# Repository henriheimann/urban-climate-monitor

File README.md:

# Urban Climate Monitor

Documentation: https://henriheimann.github.io/urban-climate-monitor/

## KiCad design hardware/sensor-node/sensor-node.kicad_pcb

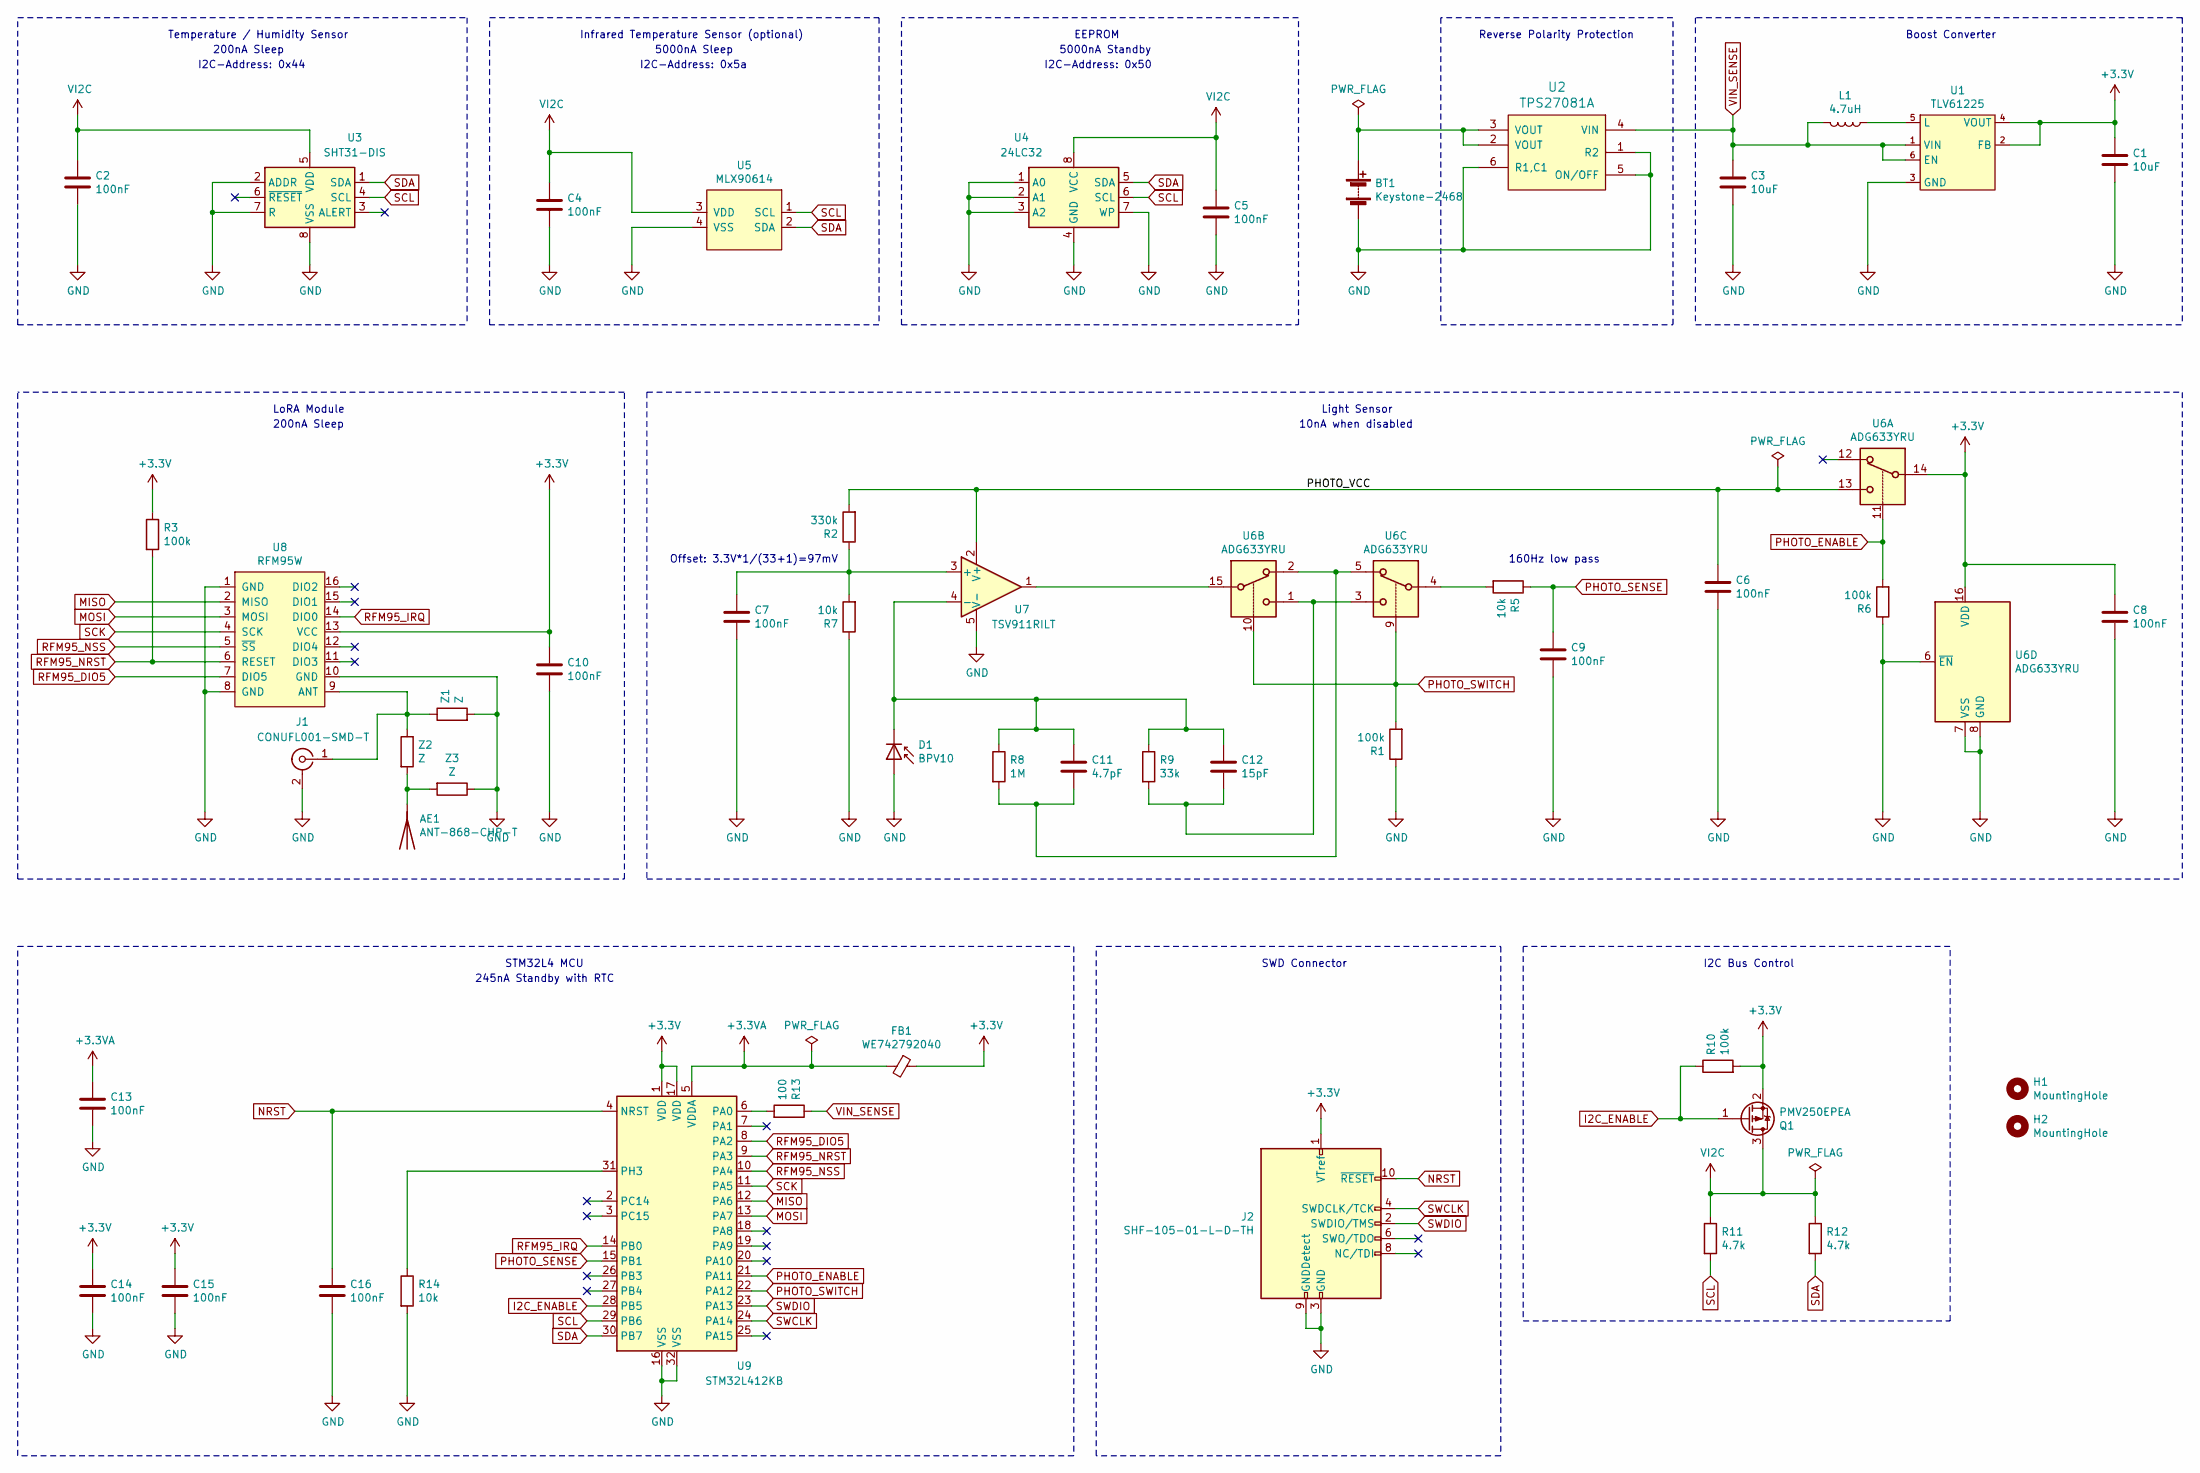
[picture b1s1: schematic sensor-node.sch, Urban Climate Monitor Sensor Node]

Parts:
AE1: ANT-868-CHP-T; Linx_ANT-868-CHP-T; mouser# 712-ANT-868-CHP-T; digikey# ANT-868-CHP-TCT-ND
BT1: Keystone-2468; BatteryHolder_Keystone_2468_2xAAA_NoSilkscreen; mouser# 534-2468; digikey# 36-2468-ND
C1, C3: 10uF; C_0805_2012Metric_Pad1.18x1.45mm_HandSolder; mouser# 80-C0805C106K9P7210; digikey# 399-C0805C106K9PAC7210CT-ND
C2, C4, C5, C6, C7, C8, C9, C10, C13, C14, C15, C16: 100nF; C_0805_2012Metric_Pad1.18x1.45mm_HandSolder; mouser# 80-C0805C103K8R; digikey# C0805C103K8RAC7800
C11: 4.7pF; C_0805_2012Metric_Pad1.18x1.45mm_HandSolder; mouser# 80-C0805C479C8HACTU; digikey# C0805C479C8HAC7800-ND
C12: 15pF; C_0805_2012Metric_Pad1.18x1.45mm_HandSolder; mouser# 80-C0805C150M8HACTU; digikey# C0805C150M8HAC7800
D1: BPV10; LED_D5.0mm_Clear; mouser# 782-BPV10; digikey# 751-1001-ND
FB1: WE742792040; L_0805_2012Metric_Pad1.15x1.40mm_HandSolder; mouser# 710-742792040; digikey# 732-1620-1-ND
H1, H2: MountingHole; MountingHole_2.2mm_M2
J1: CONUFL001-SMD-T; CONUFL001-SMD; mouser# 712-CONUFL001-SMD-T; digikey# CONUFL001-SMD-TCT-ND
J2: SHF-105-01-L-D-TH; mouser# 200-SHF10501LDTH; digikey# SAM11769-ND
L1: 4.7uH; L_Bourns-SRN4018_With3DModel; mouser# 652-SRN4018TA-4R7M; digikey# SRN4018TA-4R7MTR-ND
Q1: PMV250EPEA; SOT-23; mouser# 771-PMV250EPEAR; digikey# 1727-2303-1-ND
R1, R6: 100k; R_0805_2012Metric_Pad1.20x1.40mm_HandSolder; mouser# 603-RC0805FR-0710KL; digikey# 311-10.0KCRCT-ND
R2: 330k; R_0805_2012Metric_Pad1.20x1.40mm_HandSolder; mouser# 603-RC0805FR-07330KL; digikey# 311-330KCRCT-ND
R3, R10: 100k; R_0805_2012Metric_Pad1.20x1.40mm_HandSolder; mouser# 603-RC0805FR-07100KL; digikey# 311-100KCRCT-ND
R5, R7, R14: 10k; R_0805_2012Metric_Pad1.20x1.40mm_HandSolder; mouser# 603-RC0805FR-0710KL; digikey# 311-10.0KCRCT-ND
R8: 1M; R_0805_2012Metric_Pad1.20x1.40mm_HandSolder; mouser# 603-RC0805FR-071ML; digikey# 311-1.00MCRCT-ND
R9: 33k; R_0805_2012Metric_Pad1.20x1.40mm_HandSolder; mouser# 603-RC0805FR-0733KL; digikey# 311-33.0KCRCT-ND
R11, R12: 4.7k; R_0805_2012Metric_Pad1.20x1.40mm_HandSolder; mouser# 603-RC0805FR-074K7L; digikey# 311-4.70KCRCT-ND
R13: 100; R_0805_2012Metric_Pad1.15x1.40mm_HandSolder; mouser# 603-RC0805FR-07100RL; digikey# 311-100CRCT-ND
U1: TLV61225; SC-70-6; mouser# 595-TLV61225DCKR; digikey# 296-36756-1-ND
U2: TPS27081A; TSOT-23-6; mouser# 595-TPS27081ADDCR; digikey# 296-34970-1-ND
U3: SHT31-DIS; Sensirion_DFN-8-1EP_2.5x2.5mm_P0.5mm_EP1.1x1.7mm; mouser# 403-SHT31-DIS-F; digikey# 1649-1066-1-ND
U4: 24LC32; SOIC-8_3.9x4.9mm_P1.27mm; mouser# 579-24LC32AT-I/SN; digikey# 24LC32AT-I/SNCT-ND
U5: MLX90614; TO-39-4; mouser# 482-90614ESFBCC000TU; digikey# MLX90614ESF-BCC-000-TU-ND
U6: ADG633YRU; TSSOP-16_4.4x5mm_P0.65mm; mouser# 584-ADG633YRUZ; digikey# ADG633YRUZ-ND
U7: TSV911RILT; SOT-23-5; mouser# 511-TSV911RILT; digikey# 497-10538-1-ND
U8: RFM95W; mouser# 223-RFM95W-868S2; digikey# RFM95W-868S2-ND
U9: STM32L412KB; LQFP-32_7x7mm_P0.8mm; mouser# 511-STM32L412KBT6; digikey# 497-18229-ND
Z1, Z2, Z3: Z; R_0805_2012Metric_Pad1.20x1.40mm_HandSolder

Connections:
+3.3VA: C13.1, FB1.2, U9.5 (VDDA)
+3V3: C1.1, C8.1, C10.1, C14.1, C15.1, FB1.1, J2.1 (VTref), Q1.2 (S), R3.1, R10.2, U1.2 (FB), U1.4 (VOUT), U6.14, U6.16 (VDD), U8.13 (VCC), U9.1 (VDD), U9.17 (VDD)
/PHOTO_VCC: C6.1, R2.2, U6.13, U7.2 (V+)
GND: BT1.2 (-), C1.2, C2.2, C3.2, C4.2, C5.2, C6.2, C7.2, C8.2, C9.2, C10.2, C13.2, C14.2, C15.2, C16.2, D1.2 (A), J1.2 (Ext), J2.3 (GND), J2.5 (GND), J2.9 (GNDDetect), R1.1, R6.1, R7.1, R14.2, U1.3 (GND), U2.1 (R2), U2.5 (ON/OFF), U2.6 (R1,C1), U3.2 (ADDR), U3.7 (R), U3.8 (VSS), U3.9 (VSS), U4.1 (A0), U4.2 (A1), U4.3 (A2), U4.4 (GND), U4.7 (WP), U5.4 (VSS), U6.6 (~EN), U6.7 (VSS), U6.8 (GND), U7.5 (V-), U8.1 (GND), U8.8 (GND), U8.10 (GND), U9.16 (VSS), U9.32 (VSS), Z1.2, Z3.1
I2C_ENABLE: Q1.1 (G), R10.1, U9.28 (PB5)
MISO: U8.2 (MISO), U9.12 (PA6)
MOSI: U8.3 (MOSI), U9.13 (PA7)
NRST: C16.1, J2.10 (~RESET~), U9.4 (NRST)
unnamed: AE1.1, Z2.2, Z3.2
unnamed: BT1.1 (+), U2.2 (VOUT), U2.3 (VOUT)
unnamed: C7.1, R2.1, R7.2, U7.3 (+)
unnamed: C11.1, C12.1, D1.1 (K), R8.1, R9.1, U7.4 (-)
unnamed: C11.2, R8.2, U6.2, U6.5
unnamed: C12.2, R9.2, U6.1, U6.3
unnamed: J1.1 (In), U8.9 (ANT), Z1.1, Z2.1
unnamed: L1.1, U1.5 (L)
unnamed: R5.2, U6.4
unnamed: R13.2, U9.6 (PA0)
unnamed: R14.1, U9.31 (PH3)
unnamed: U6.15, U7.1
PHOTO_ENABLE: R6.2, U6.11, U9.21 (PA11)
PHOTO_SENSE: C9.1, R5.1, U9.15 (PB1)
PHOTO_SWITCH: R1.2, U6.9, U6.10, U9.22 (PA12)
RFM95_DIO5: U8.7 (DIO5), U9.8 (PA2)
RFM95_IRQ: U8.14 (DIO0), U9.14 (PB0)
RFM95_NRST: R3.2, U8.6 (RESET), U9.9 (PA3)
RFM95_NSS: U8.5 (~SS), U9.10 (PA4)
SCK: U8.4 (SCK), U9.11 (PA5)
SCL: R11.2, U3.4 (SCL), U4.6 (SCL), U5.1 (SCL), U9.29 (PB6)
SDA: R12.2, U3.1 (SDA), U4.5 (SDA), U5.2 (SDA), U9.30 (PB7)
SWCLK: J2.4 (SWDCLK/TCK), U9.24 (PA14)
SWDIO: J2.2 (SWDIO/TMS), U9.23 (PA13)
VI2C: C2.1, C4.1, C5.1, Q1.3 (D), R11.1, R12.1, U3.5 (VDD), U4.8 (VCC), U5.3 (VDD)
VIN_SENSE: C3.1, L1.2, R13.1, U1.1 (VIN), U1.6 (EN), U2.4 (VIN)

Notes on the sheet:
Reverse Polarity Protection
Boost Converter
SWD Connector
STM32L4 MCU
I2C-Address: 0x44
I2C-Address: 0x5a
Offset: 3.3V*1/(33+1)=97mV
Infrared Temperature Sensor (optional)
Temperature / Humidity Sensor
LoRA Module
Light Sensor
I2C-Address: 0x50
EEPROM
5000nA Sleep
200nA Sleep
5000nA Standby
245nA Standby with RTC
10nA when disabled
160Hz low pass
I2C Bus Control

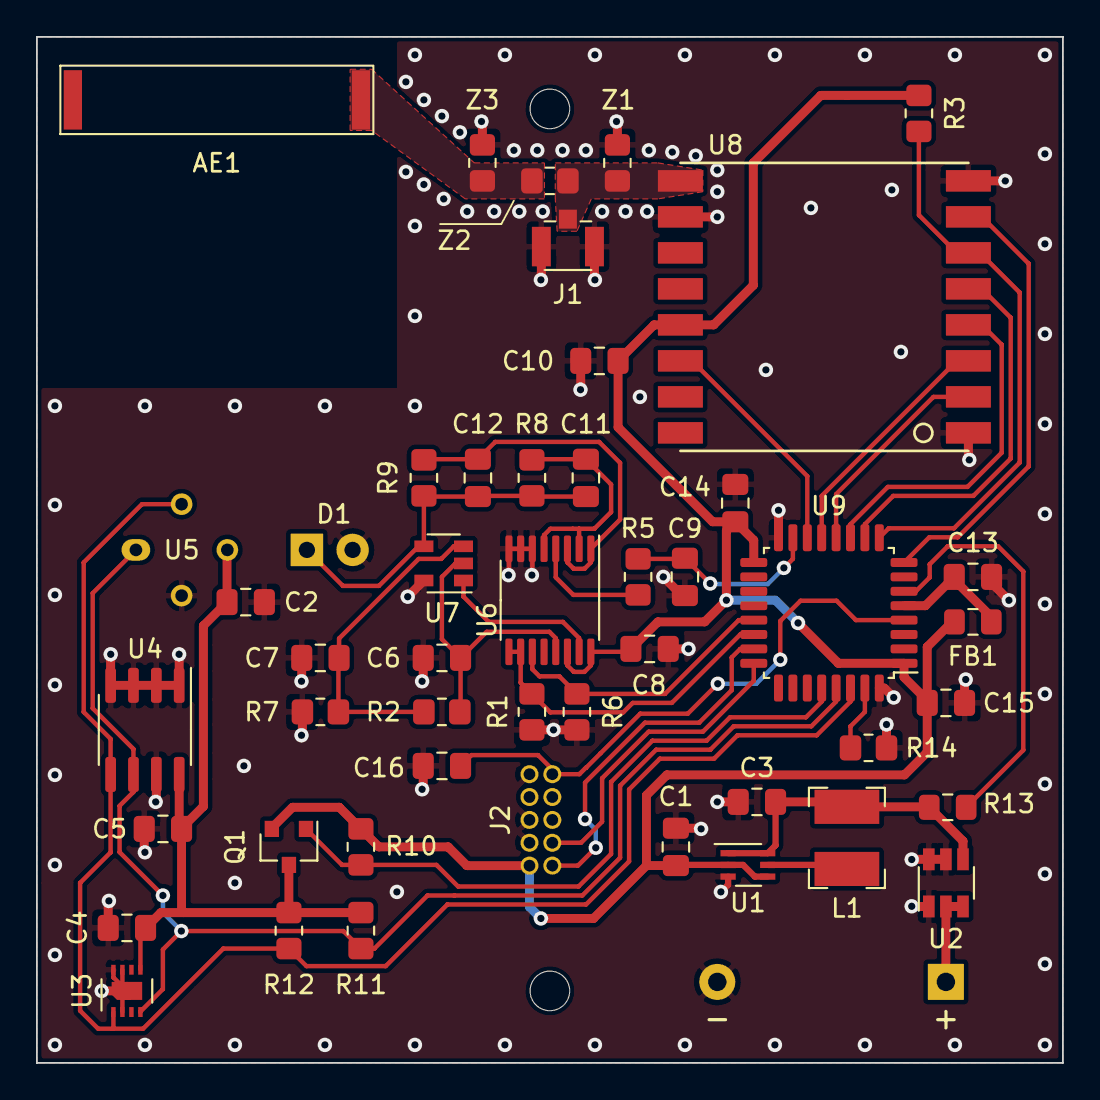
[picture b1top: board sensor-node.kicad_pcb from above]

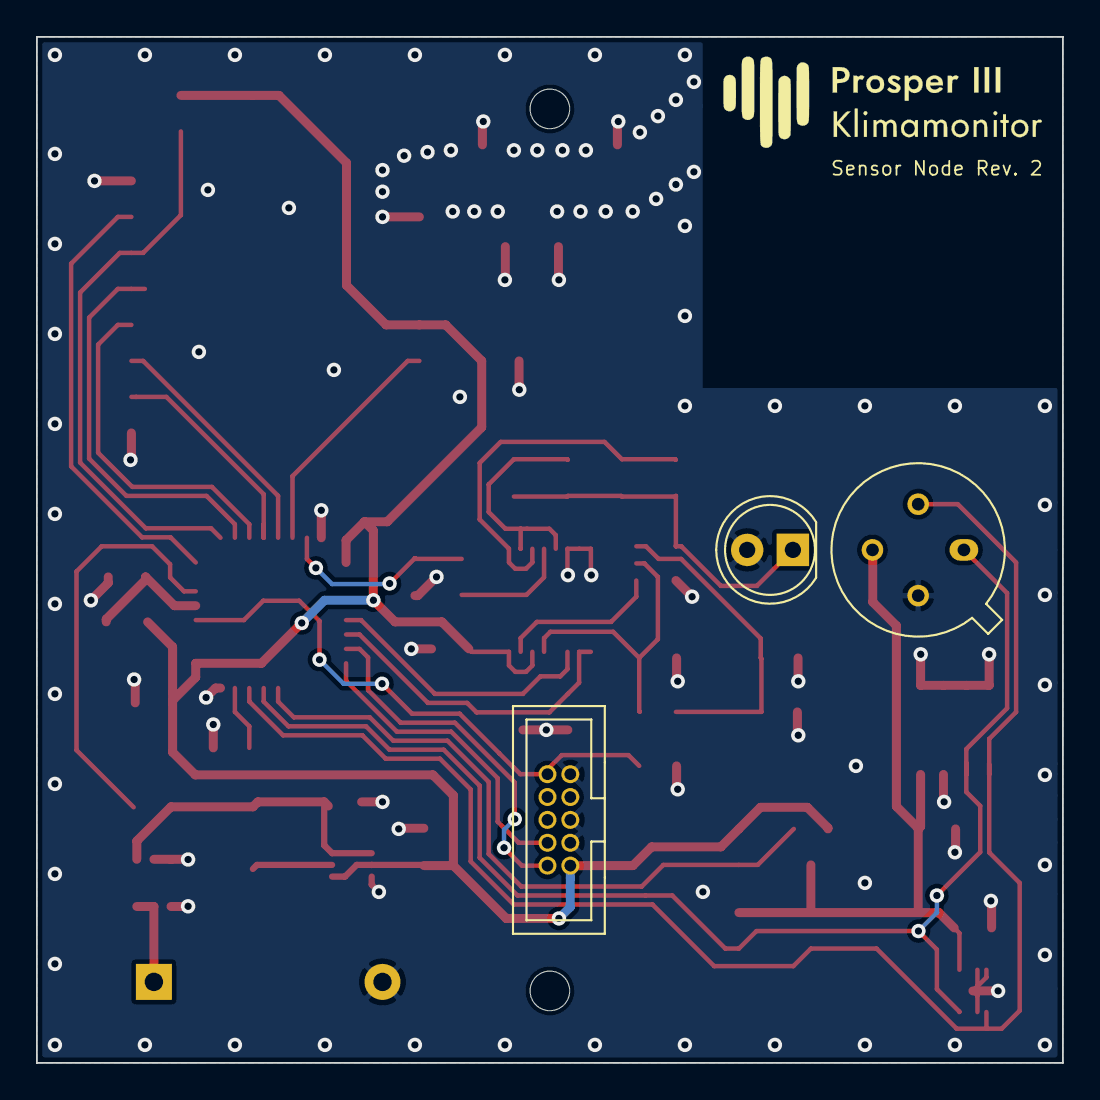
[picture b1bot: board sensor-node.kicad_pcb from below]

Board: 2 copper layers, 57.0 x 57.0 mm, 51 parts (4 on the bottom side), 34 nets.

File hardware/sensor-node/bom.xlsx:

| Number of Boards: | 3
Source | Reference | Value | Quantity Abs | Quantity | Manufacturer # | Digikey # | Digikey STK | Mouser # | Mouser STK | Price
BOM | AE1 |  |  | 1 | ANT-868-CHP-T | ANT-868-CHP-TCT-ND | 2.3199999999999998 |  |  | 6.9599999999999991
BOM | BT1 |  |  | 1 | 2468 |  |  | 534-2468 | 1.1499999999999999 | 3.4499999999999997
BOM | C11 | 4.7pF |  | 1 | C0805C479C8HACTU |  |  | 80-C0805C479C8HACTU | 8.5000000000000006E-2 | 0.255
BOM | C12 | 15pF |  | 1 | C0805C150M8HACTU |  |  | 80-C0805C150M8HACTU | 8.5000000000000006E-2 | 0.255
BOM | C2 C4 C5 C6 C7 C8 C9 C10 C13 C14 C15 C16 | 100nF |  | 12 | C0805C103K8RACTU |  |  | 80-C0805C103K8R | 0.152 | 5.4719999999999995
BOM | C1 C3 | 10uF |  | 2 | C0805C106K9PAC7210 |  |  | 80-C0805C106K9P7210 | 0.11899999999999999 | 0.71399999999999997
BOM | D1 |  |  | 1 | BPV10 |  |  | 782-BPV10 | 0.93200000000000005 | 2.7960000000000003
BOM | FB1 |  |  | 1 | 742792040 |  |  | 710-742792040 | 0.186 | 0.55800000000000005
BOM | J1 |  |  | 1 | CONUFL001-SMD-T |  |  | 712-CONUFL001-SMD-T | 0.52500000000000002 | 1.5750000000000002
BOM | J2 |  |  | 1 | SHF-105-01-L-D-TH |  |  | 200-SHF10501LDTH | 2.29 | 6.87
BOM | L1 | 4.7uH |  | 1 | SRN4018TA-4R7M | SRN4018TA-4R7MCT-ND | 0.41 |  |  | 1.23
BOM | Q1 |  |  | 1 | PMV250EPEA |  |  | 771-PMV250EPEAR | 0.34 | 1.02
BOM | R11 R12 | 4.7k |  | 2 | RC0805FR-074K7L |  |  | 603-RC0805FR-074K7L | 0.11 | 0.66
BOM | R13 | 100 |  | 1 | RC0805FR-07100RL |  |  | 603-RC0805FR-07100RL | 0.11 | 0.33
BOM | R5 R6 R7 R14 | 10k |  | 4 | RC0805FR-0710KL |  |  | 603-RC0805FR-0710KL | 0.11 | 1.32
BOM | R2 | 330k |  | 1 | RC0805FR-07330KL |  |  | 603-RC0805FR-07330KL | 0.11 | 0.33
BOM | R3 R4 R10 | 100k |  | 3 | RC0805FR-07100KL |  |  | 603-RC0805FR-07100KL | 0.11 | 0.99
BOM | R8 | 1M |  | 1 | RC0805FR-071ML |  |  | 603-RC0805FR-071ML | 8.5000000000000006E-2 | 0.255
BOM | R9 | 33k |  | 1 | RC0805FR-0733KL |  |  | 603-RC0805FR-0733KL | 0.11 | 0.33
BOM | U1 |  |  | 1 | TLV61225DCKR |  |  | 595-TLV61225DCKR | 0.86 | 2.58
BOM | U2 |  |  | 1 | TPS27081ADDCR |  |  | 595-TPS27081ADDCR | 0.66 | 1.98
BOM | U3 |  |  | 1 | SHT31-DIS-F2.5kS |  |  | 403-SHT31-DIS-F | 5.4 | 16.200000000000003
BOM | U4 |  |  | 1 | 24LC32AT-I/SN |  |  | 579-24LC32AT-I/SN | 0.28799999999999998 | 0.86399999999999988
BOM | U5 |  |  | 1 | MLX90614ESF-BCC-000-TU | MLX90614ESF-BCC-000-TU-ND | 20.78 |  |  | 62.34
BOM | U6 |  |  | 1 | ADG633YRUZ |  |  | 584-ADG633YRUZ | 2.2400000000000002 | 6.7200000000000006
BOM | U7 |  |  | 1 | TSV911RILT |  |  | 511-TSV911RILT | 0.63 | 1.8900000000000001
BOM | U8 |  |  | 1 | RFM95W-868 | RFM95W-868S2-ND | 12.2 |  |  | 36.599999999999994
BOM | U9 |  |  | 1 | STM32L412KBT6 |  |  | 511-STM32L412KBT6 | 3.06 | 9.18
EQUIP |  |  | 1 |  | CSH-SGFB-100-UFFR |  |  | 712-CSH-SGFB100-UFFR | 4.87 | 4.87
EQUIP |  |  | 1 |  | ADP-SMAM-SMAM-G |  |  | 712-ADP-SMAM-SMAM-G | 5.52 | 5.52
 |  |  |  |  |  |  |  |  |  | 184.114

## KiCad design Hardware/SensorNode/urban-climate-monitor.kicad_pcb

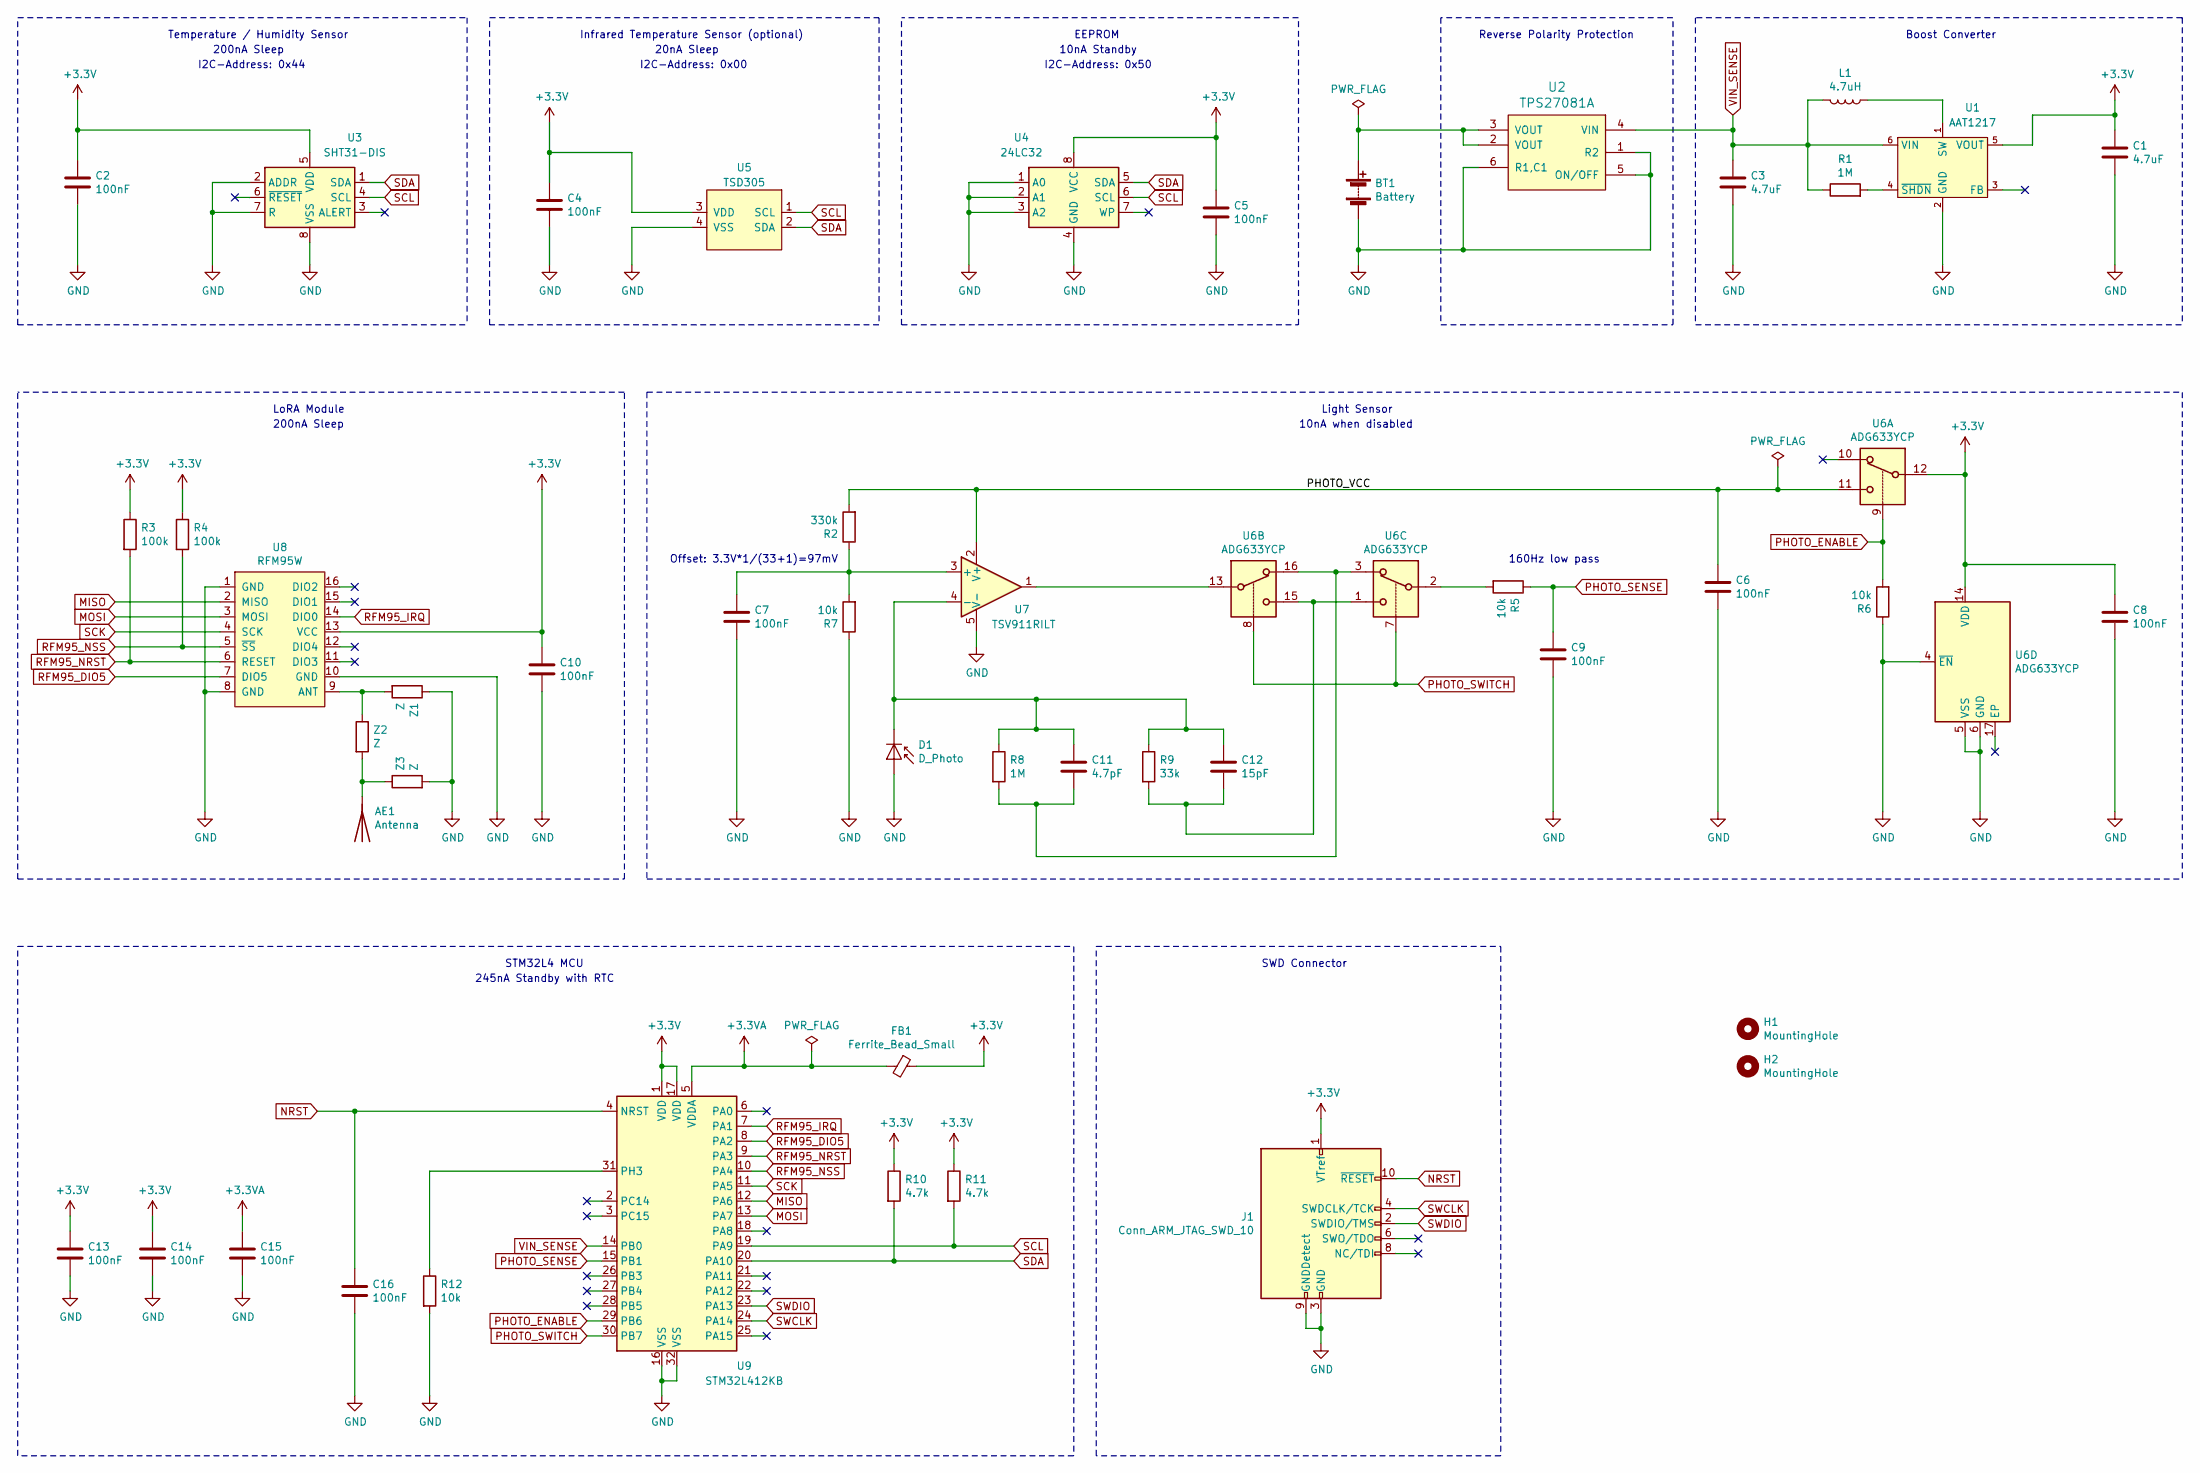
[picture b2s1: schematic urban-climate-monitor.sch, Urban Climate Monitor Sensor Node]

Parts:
AE1: Antenna; 868MHZ_TI_DNO24
BT1: Battery; BatteryHolder_Keystone_2468_2xAAA_NoSilkscreen
C1, C3: 4.7uF; C_0805_2012Metric_Pad1.18x1.45mm_HandSolder
C2, C4, C5, C6, C7, C8, C9, C10, C13, C14, C15, C16: 100nF; C_0805_2012Metric_Pad1.18x1.45mm_HandSolder
C11: 4.7pF; C_0805_2012Metric_Pad1.18x1.45mm_HandSolder
C12: 15pF; C_0805_2012Metric_Pad1.18x1.45mm_HandSolder
D1: D_Photo; LED_D5.0mm_Clear
FB1: Ferrite_Bead_Small; L_0805_2012Metric_Pad1.05x1.20mm_HandSolder
H1, H2: MountingHole; MountingHole_2.2mm_M2
J1: Conn_ARM_JTAG_SWD_10; Amphenol_FCI_ShroudedSocket_2x05_P1.27mm_Vertical_SMD
L1: 4.7uH; L_Bourns-SRN4018_With3DModel
R1, R8: 1M; R_0805_2012Metric_Pad1.20x1.40mm_HandSolder
R2: 330k; R_0805_2012Metric_Pad1.20x1.40mm_HandSolder
R3, R4: 100k; R_0805_2012Metric_Pad1.20x1.40mm_HandSolder
R5, R6, R7, R12: 10k; R_0805_2012Metric_Pad1.20x1.40mm_HandSolder
R9: 33k; R_0805_2012Metric_Pad1.20x1.40mm_HandSolder
R10, R11: 4.7k; R_0805_2012Metric_Pad1.20x1.40mm_HandSolder
U1: AAT1217; TSOT-23-6_HandSoldering
U2: TPS27081A; TSOT-23-6_HandSoldering
U3: SHT31-DIS; Sensirion_DFN-8-1EP_2.5x2.5mm_P0.5mm_EP1.1x1.7mm
U4: 24LC32; SOIC-8_3.9x4.9mm_P1.27mm
U5: TSD305
U6: ADG633YCP; TSSOP-16_4.4x5mm_P0.65mm
U7: TSV911RILT; SOT-23-5
U8: RFM95W
U9: STM32L412KB; LQFP-32_7x7mm_P0.8mm
Z1, Z2, Z3: Z; R_0805_2012Metric_Pad1.20x1.40mm_HandSolder

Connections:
+3.3VA: C15.1, FB1.2, U9.5 (VDDA)
+3V3: C1.1, C2.1, C4.1, C5.1, C8.1, C10.1, C13.1, C14.1, FB1.1, J1.1 (VTref), R3.1, R4.1, R10.1, R11.1, U1.5 (VOUT), U3.5 (VDD), U4.8 (VCC), U5.3 (VDD), U6.12, U6.14 (VDD), U8.13 (VCC), U9.1 (VDD), U9.17 (VDD)
/PHOTO_VCC: C6.1, R2.2, U6.11, U7.2 (V+)
GND: BT1.2 (-), C1.2, C2.2, C3.2, C4.2, C5.2, C6.2, C7.2, C8.2, C9.2, C10.2, C13.2, C14.2, C15.2, C16.2, D1.2 (A), J1.3 (GND), J1.5 (GND), J1.9 (GNDDetect), R6.1, R7.1, R12.2, U1.2 (GND), U2.1 (R2), U2.5 (ON/OFF), U2.6 (R1,C1), U3.2 (ADDR), U3.7 (R), U3.8 (VSS), U3.9 (VSS), U4.1 (A0), U4.2 (A1), U4.3 (A2), U4.4 (GND), U5.4 (VSS), U6.4 (~EN), U6.5 (VSS), U6.6 (GND), U7.5 (V-), U8.1 (GND), U8.8 (GND), U8.10 (GND), U9.16 (VSS), U9.32 (VSS), Z1.1, Z3.2
MISO: U8.2 (MISO), U9.12 (PA6)
MOSI: U8.3 (MOSI), U9.13 (PA7)
NRST: C16.1, J1.10 (~RESET~), U9.4 (NRST)
unnamed: AE1.1, Z2.2, Z3.1
unnamed: BT1.1 (+), U2.2 (VOUT), U2.3 (VOUT)
unnamed: C7.1, R2.1, R7.2, U7.3 (+)
unnamed: C11.1, C12.1, D1.1 (K), R8.1, R9.1, U7.4 (-)
unnamed: C11.2, R8.2, U6.3, U6.16
unnamed: C12.2, R9.2, U6.1, U6.15
unnamed: L1.1, U1.1 (SW)
unnamed: R1.2, U1.4 (~SHDN)
unnamed: R5.2, U6.2
unnamed: R12.1, U9.31 (PH3)
unnamed: U6.13, U7.1
unnamed: U8.9 (ANT), Z1.2, Z2.1
PHOTO_ENABLE: R6.2, U6.9, U9.29 (PB6)
PHOTO_SENSE: C9.1, R5.1, U9.15 (PB1)
PHOTO_SWITCH: U6.7, U6.8, U9.30 (PB7)
RFM95_DIO5: U8.7 (DIO5), U9.8 (PA2)
RFM95_IRQ: U8.14 (DIO0), U9.7 (PA1)
RFM95_NRST: R3.2, U8.6 (RESET), U9.9 (PA3)
RFM95_NSS: R4.2, U8.5 (~SS), U9.10 (PA4)
SCK: U8.4 (SCK), U9.11 (PA5)
SCL: R11.2, U3.4 (SCL), U4.6 (SCL), U5.1 (SCL), U9.19 (PA9)
SDA: R10.2, U3.1 (SDA), U4.5 (SDA), U5.2 (SDA), U9.20 (PA10)
SWCLK: J1.4 (SWDCLK/TCK), U9.24 (PA14)
SWDIO: J1.2 (SWDIO/TMS), U9.23 (PA13)
VIN_SENSE: C3.1, L1.2, R1.1, U1.6 (VIN), U2.4 (VIN), U9.14 (PB0)

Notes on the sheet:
Reverse Polarity Protection
Boost Converter
SWD Connector
STM32L4 MCU
I2C-Address: 0x44
I2C-Address: 0x00
Offset: 3.3V*1/(33+1)=97mV
Infrared Temperature Sensor (optional)
Temperature / Humidity Sensor
LoRA Module
Light Sensor
I2C-Address: 0x50
EEPROM
20nA Sleep
200nA Sleep
10nA Standby
245nA Standby with RTC
10nA when disabled
160Hz low pass

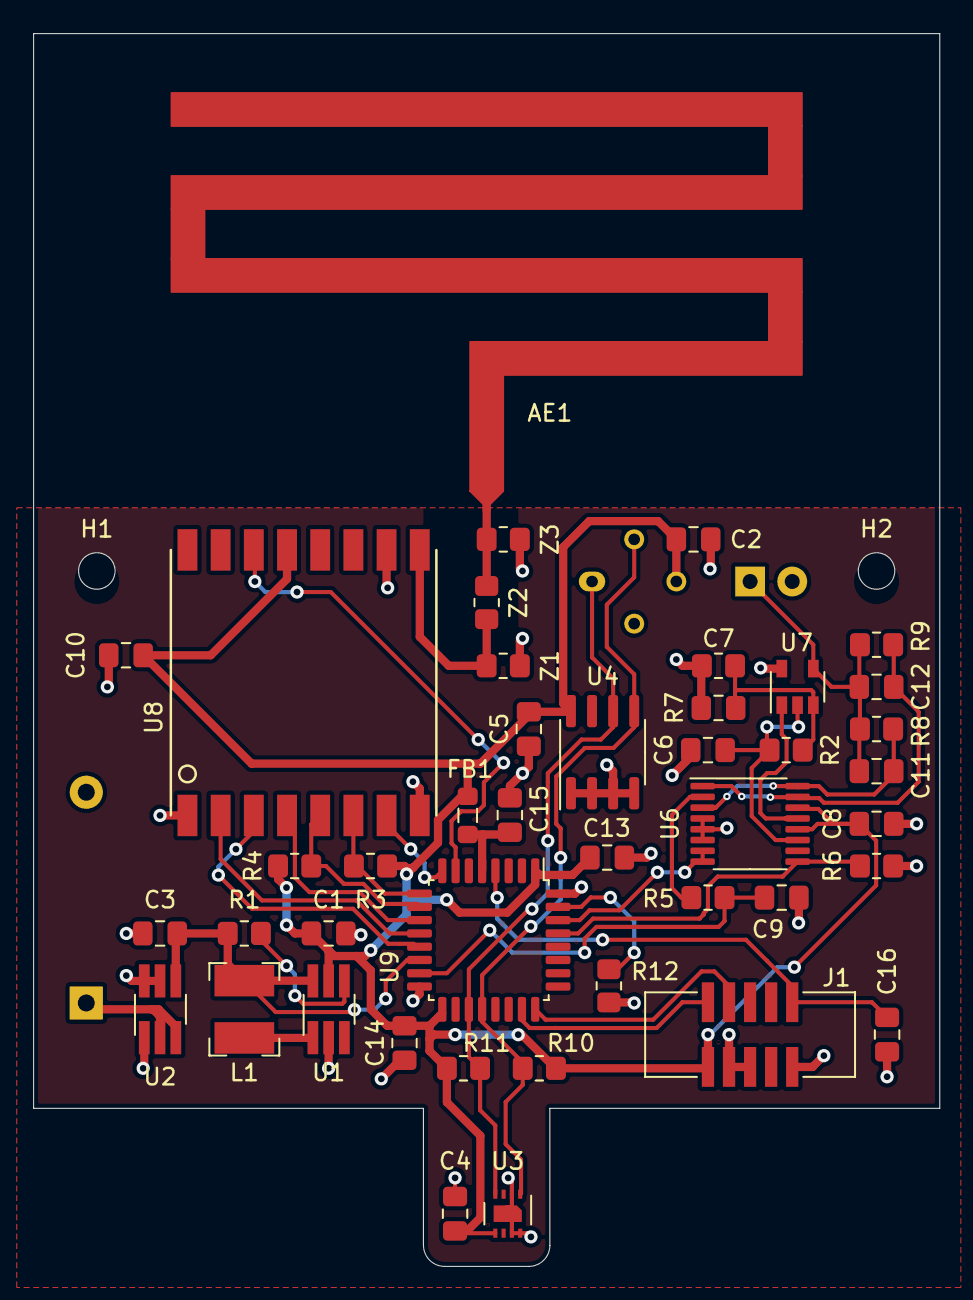
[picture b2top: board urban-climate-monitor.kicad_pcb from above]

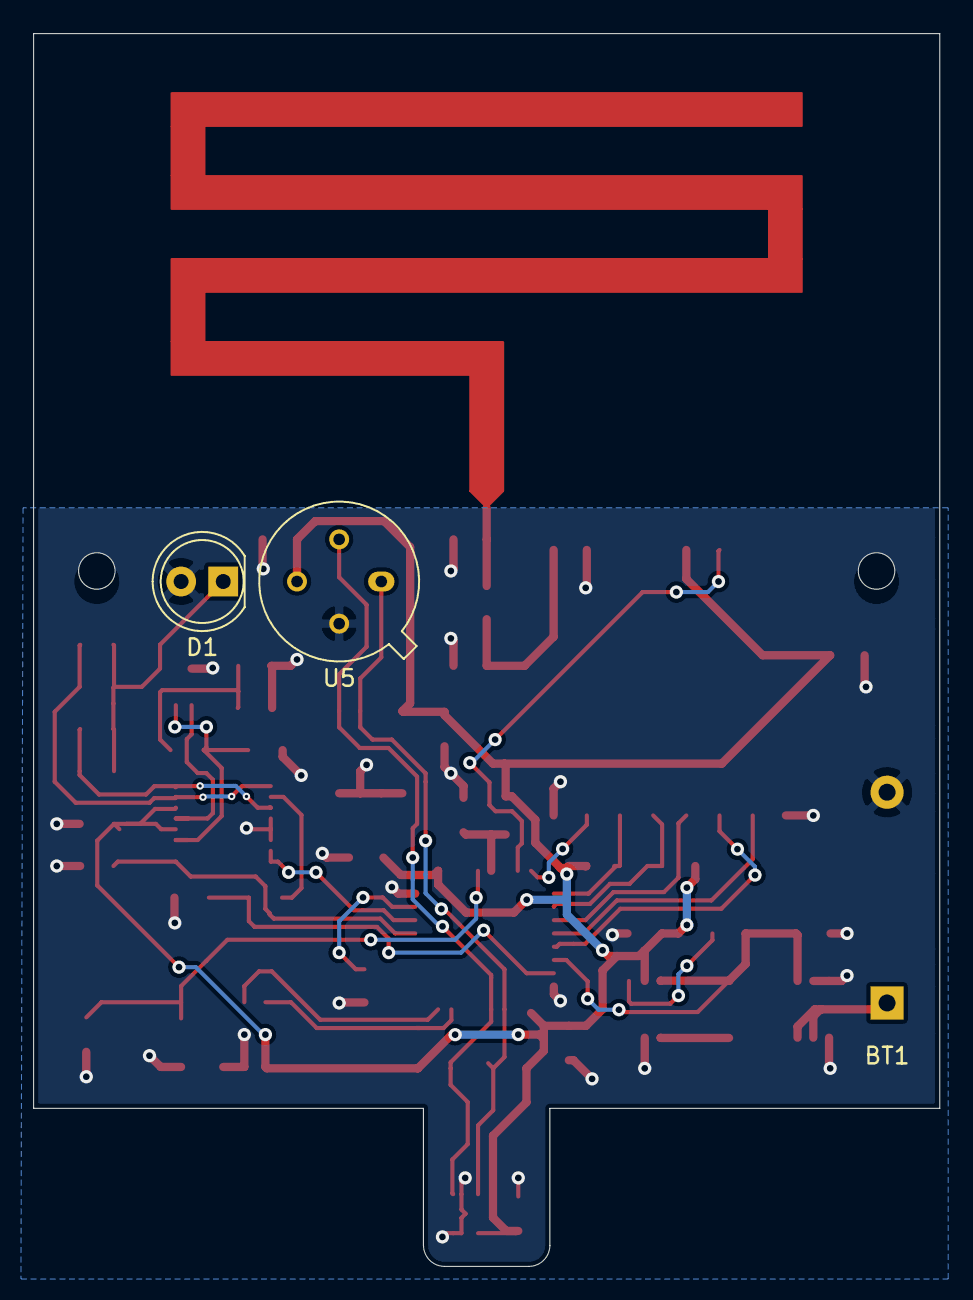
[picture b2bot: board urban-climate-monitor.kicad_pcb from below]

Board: 2 copper layers, 54.6 x 74.3 mm, 48 parts (3 on the bottom side), 32 nets.

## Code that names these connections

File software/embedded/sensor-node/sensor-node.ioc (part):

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PA0-CK_IN.GPIO_Label=VIN_SENSE
PA0-CK_IN.GPIOParameters=GPIO_Label
PA2.GPIO_PuPd=GPIO_PULLUP
PA6.Mode=Full_Duplex_Master
PA14\ (JTCK/SWCLK).GPIOParameters=GPIO_Label
Mcu.UserName=STM32L412KBUx
PA12.GPIOParameters=GPIO_PuPd,GPIO_Label
PA11.GPIOParameters=GPIO_Label
PA3.GPIOParameters=GPIO_Label
PB0.GPIO_Label=RFM95_DIO0
PA2.GPIOParameters=GPIO_PuPd,GPIO_Label
PB5.GPIOParameters=PinState,GPIO_Label
PA14\ (JTCK/SWCLK).Signal=SYS_JTCK-SWCLK
PA12.Signal=GPIO_Output
PB6.Signal=I2C1_SCL
PB5.PinState=GPIO_PIN_SET
PB6.Mode=I2C
RCC.HSE_VALUE=8000000
PA0-CK_IN.Signal=ADCx_IN5
PB0.GPIOParameters=GPIO_PuPd,GPIO_Label
PA13\ (JTMS/SWDIO).GPIO_Label=SWDIO
PB1.GPIO_Label=PHOTO_SENSE
PB7.Signal=I2C1_SDA
PA14\ (JTCK/SWCLK).Mode=Serial_Wire
PB6.GPIO_PuPdOD=GPIO_NOPULL
PB6.GPIOParameters=GPIO_PuPdOD
Mcu.Package=UFQFPN32
PA6.Signal=SPI1_MISO
PB1.Signal=ADCx_IN16
PA2.GPIO_Label=RFM95_DIO5
PA14\ (JTCK/SWCLK).GPIO_Label=SWCLK
PB5.GPIO_Label=I2C_ENABLE
PA12.GPIO_PuPd=GPIO_PULLDOWN
PA4.GPIO_Label=RFM95_NSS
PA3.Signal=GPIO_Output
PA5.Mode=Full_Duplex_Master
PA7.Mode=Full_Duplex_Master
PA13\ (JTMS/SWDIO).Mode=Serial_Wire
PA11.GPIO_Label=PHOTO_ENABLE
boardIOC=true
PA13\ (JTMS/SWDIO).GPIOParameters=GPIO_Label
PA12.GPIO_Label=PHOTO_SWITCH
PA4.PinState=GPIO_PIN_SET
PB7.GPIOParameters=GPIO_PuPdOD
PA5.Signal=SPI1_SCK
board=NUCLEO-L412KB
PA4.GPIOParameters=PinState,GPIO_Label
PB7.GPIO_PuPdOD=GPIO_NOPULL
Mcu.Name=STM32L412KBUx
PA2.Signal=GPIO_Input
PA4.Signal=GPIO_Output
RCC.SYSCLKFreq_VALUE=32000000
PB5.Signal=GPIO_Output
PB7.Mode=I2C
PA11.Signal=GPIO_Output
PB0.Signal=GPIO_Input
PB0.GPIO_PuPd=GPIO_PULLUP
PA13\ (JTMS/SWDIO).Signal=SYS_JTMS-SWDIO
PA3.GPIO_Label=RFM95_NRST
PB1.GPIOParameters=GPIO_Label
PA7.Signal=SPI1_MOSI

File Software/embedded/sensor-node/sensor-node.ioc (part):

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PA6.Mode=Full_Duplex_Master
PA14\ (JTCK/SWCLK).GPIOParameters=GPIO_Label
Mcu.UserName=STM32L412KBUx
PA3.GPIOParameters=PinState,GPIO_Label
PB0.GPIO_Label=VIN_SENSE
PB6.GPIO_Label=PHOTO_ENABLE
PA2.GPIOParameters=GPIO_Label
PA14\ (JTCK/SWCLK).Signal=SYS_JTCK-SWCLK
PB6.Signal=GPIO_Output
RCC.HSE_VALUE=8000000
PB0.GPIOParameters=GPIO_Label
PA13\ (JTMS/SWDIO).GPIO_Label=SWDIO
PA1.GPIOParameters=GPIO_Label
PB1.GPIO_Label=PHOTO_SENSE
PB7.Signal=GPIO_Output
PA14\ (JTCK/SWCLK).Mode=Serial_Wire
PB6.GPIOParameters=GPIO_Label
PB7.GPIO_Label=PHOTO_SWITCH
Mcu.Package=UFQFPN32
PA6.Signal=SPI1_MISO
PB1.Signal=ADCx_IN16
PA2.GPIO_Label=RFM95_DIO5
PA10.Signal=I2C1_SDA
PA14\ (JTCK/SWCLK).GPIO_Label=SWCLK
PA4.GPIO_Label=RFM95_NSS
PA3.Signal=GPIO_Output
PA5.Mode=Full_Duplex_Master
PA7.Mode=Full_Duplex_Master
PA13\ (JTMS/SWDIO).Mode=Serial_Wire
PA10.Mode=I2C
boardIOC=true
PA13\ (JTMS/SWDIO).GPIOParameters=GPIO_Label
PA9.Mode=I2C
PA4.PinState=GPIO_PIN_SET
PB7.GPIOParameters=GPIO_Label
PA9.Signal=I2C1_SCL
PA1.Signal=GPXTI1
PA5.Signal=SPI1_SCK
board=NUCLEO-L412KB
PA1.GPIO_Label=RFM95_IRQ
PA4.GPIOParameters=PinState,GPIO_Label
Mcu.Name=STM32L412KBUx
PA2.Signal=GPIO_Input
PA4.Signal=GPIO_Output
RCC.SYSCLKFreq_VALUE=32000000
PA3.PinState=GPIO_PIN_SET
PB0.Signal=ADCx_IN15
PA13\ (JTMS/SWDIO).Signal=SYS_JTMS-SWDIO
PA3.GPIO_Label=RFM95_NRST
PB1.GPIOParameters=GPIO_Label
PA7.Signal=SPI1_MOSI

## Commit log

2020-10-19 Add initial embedded software version and update schematic
2020-10-23 Update prototype pin assignment
2020-10-23 Add required submodules to prototype project
2020-10-23 Hello world from MCU
2020-10-26 Remove rfm9x submodule, sht3x test in main application
2020-10-26 Add new rfm95 submodule
2020-10-26 Move embedded projects to subdirectory
2020-10-26 Update submodules for new subdirectory
2020-10-26 Ignore build directory, update cmake workflow
2020-10-26 Checkout submodules in cmake_urbanclimatemonitorprototype.yml
2020-10-26 Rename prototype project to PrototypeNode
2020-10-26 Initial work on rfm95 integration
2020-10-29 Updates RFM95 integration and first test
2020-10-30 Update rfm95 library version
2020-10-30 Add lora frame couting via eeprom
2020-10-30 Include EEPROM in schematic
2020-10-30 Add photo sensing implementation
2020-11-02 Create first revision of PCB, add CubeMX project for PCB sensor node
2020-11-02 Update directory structure
2020-11-03 Test KiCad action docs generation
2020-11-03 Trigger pipeline
2020-11-03 Fix warnings of electrical rules check
2020-11-11 Add photo enable pin, add deployment compose
2020-11-11 Upload only pdfs as artifact
2020-11-11 Fix pipeline docs path
2020-11-12 Add TIG stack to deployment
2020-11-12 Move grafana behind nginx reverse proxy
2020-11-12 Add deployment readme
2020-11-12 Add angular frontend
2020-11-12 Add frontend to deployment
2020-11-12 Create deploy script
2020-11-12 Add SSL to deployed site
2020-11-12 Add ssl renew cron
2020-11-15 Change folder layout, add new version pcb layout
2020-11-15 Fix folder capitalisation
2020-11-15 Try fix folder capitalisation again part 1
2020-11-15 Try fix folder capitalisation again part 2
2020-11-15 Try fix submodules part 1
2020-11-15 Try fix submodules part 2
2020-11-16 Add standby mode between measurements and photocurrent measurement
2020-11-19 Update schema to include I2C voltage switching
2020-11-19 Update PCB, add debugging printouts to application
2020-11-19 Test export of board plot
2020-11-19 Fix workflow schematic and board references
2020-11-19 Only upload required files
2020-11-20 Fix timeouts for systick overflow handling
2020-11-21 Update PCB for enclosure
2020-11-22 Add 3d model to infrared temperature sensor
2020-11-22 Add design resources and logo to PCB silkscreen
2020-11-28 Add picket fence vias
2020-11-29 Switch to available boost converter
2020-11-29 Update PCB for new boost converter
2020-11-29 Fix ERC & DRC errors
2020-11-29 Fix ADG633YRU pinout
2020-11-29 Update C9 pad 2
2020-11-29 Perform parts pinout check
2020-11-29 Add BOM excel sheet
2020-12-28 Setup sensor-node embedded project
2020-12-28 Move eeprom to submodule
2020-12-28 Update submodules remotes
2020-12-28 Add sensor-node build workflow
2020-12-31 First implementation of MLX90614 driver
2021-01-09 Work on sensor-node application
2021-01-09 Move RFM95 initialisation
2021-01-11 Fix rounding and wait for MLX90614
2021-01-11 Fix PCB problems for Rev. 2
2021-01-11 Move Via
2021-01-25 Add nanovna calibration
2021-02-26 Fix InfluxDB version to 1.8, add local test deployment possibility
2021-02-27 Add three.js canvas
2021-03-08 Add basic backend setup
2021-03-13 Update design, work on backend
2021-03-22 Work on user and sensor controllers and services
2021-03-23 Add SensorService unit tests
2021-03-23 Remove prototype embedded software
2021-03-23 Remove submodules
2021-03-23 Readd submodules
2021-03-23 Remove MLX90614 code to be replaced by submodule
2021-03-23 Add MLX90614 submodule
2021-03-23 Move embedded software back to subfolder
    * Add stm32l4.cfg for OpenOCD
    * Source TTN keys from environment when using CMake
2021-03-23 Fix workflow directory
2021-03-23 Add .gitattributes
2021-03-23 Remove telegraph from devenv, add github action for backend tests
2021-03-23 Force backend action run
2021-03-23 Update github action for backend tests
2021-03-23 Fix run command
2021-03-23 Fix deploy-local-devenv.sh permissions
2021-03-23 Add write .env file step
2021-03-23 Fix JDK version
2021-03-23 Add postgres port environment variable
2021-03-23 Don’t log maven transfer progress
2021-03-23 Ignore not implemented test for now
2021-03-25 Change submodule directory
2021-03-25 Update submodule versions
2021-03-25 Update eeprom submodule
2021-03-27 Add location controller and service
2021-03-28 Add InfluxDB testdata, add LocationControllerIntegrationTest
2021-04-01 Initial work on frontend
2021-04-07 Add auth functionallity
2021-04-15 Complete admin UI in frontend, update workflows and deployment structure
2021-04-15 Update EEPROM component, fix deployment script line endings
2021-04-15 Update workflows for documentation
2021-04-15 Force pipeline runs
2021-04-15 Deploying to gh-pages from henriheimann/urban-climate-monitor@f7450f9f9013dbe18db50a8ccf000ba61fdd8733
2021-04-15 Initial gh-pages commit
2021-04-15 Deploying hardware artifcats to gh-pages from henriheimann/urban-climate-monitor@f7450f9f9013dbe18db50a8ccf000ba61fdd8733
2021-04-15 Deploying to gh-pages from henriheimann/urban-climate-monitor@10970d79ae4631e2a290d646281c9daabca91809
2021-04-15 Fix repo path in hardware pipeline
2021-04-15 Fix kibot config paths
2021-04-15 Deploying hardware artifcats to gh-pages from henriheimann/urban-climate-monitor@0d7ab9aa95bf6e51285470499f80e2adb45ec539
2021-04-15 Add custom pcb plot style
2021-04-15 Deploying hardware artifcats to gh-pages from henriheimann/urban-climate-monitor@4486a2b831a692a09b1c9eab15fdc7a7317fe762
2021-04-20 Add system overview UML, update documentation pipeline to include assets
2021-04-20 Only copy assets folder contents
2021-04-20 Force documentation pipeline run
2021-04-20 Deploying documentation to gh-pages from henriheimann/urban-climate-monitor@40d59ce3f7d00abae7a6d105bafc2ffadd309735
2021-04-20 Set github-env attribute in documentation pipeline
2021-04-20 Deploying documentation to gh-pages from henriheimann/urban-climate-monitor@5931c325e6c893a5fbbbc325709dec5402879273
2021-04-24 Add login routing logic to frontend
2021-04-24 Deploying documentation to gh-pages from henriheimann/urban-climate-monitor@354dc0d580889ee4e4380424671c233f114ca77d
2021-04-24 Remove build folder
2021-04-25 Show TTN device keys in frontend
2021-04-26 Seperate local dev and test deployments, fix TTN device ID generation
2021-04-26 Deploying hardware artifcats to gh-pages from henriheimann/urban-climate-monitor@8e1f780825e3d8d29561fcdc01f146208aa76723
2021-04-26 Add empty TTN keys for embedded workflow
2021-04-26 Update backend pipeline environment variables
2021-04-30 Implement location sensor list
2021-05-01 Fix deploy-local-test script to include user access for metricstest
2021-05-09 Cleanup frontend code, switch to eslint and prettier
2021-05-10 Refactor location entity logic, no longer use JWT token, finish edit sensors logic
2021-05-10 Update documentation style
2021-05-10 Deploying documentation to gh-pages from henriheimann/urban-climate-monitor@a47a648b01a1b0459a9bdd912de601f9fdce62d4
2021-05-11 Update documentation
2021-05-11 Deploying documentation to gh-pages from henriheimann/urban-climate-monitor@93fa838896816310e5fc8390be49cb5fd7185917
2021-05-15 Start working on location measurements display
2021-05-15 Deploying documentation to gh-pages from henriheimann/urban-climate-monitor@0db51ba9c2b8e4872d70ac99b6f0b6ff09eeaf1f
2021-05-22 Get single sensor measurements
2021-05-24 Start work on visualisation
2021-05-30 Add sensor measurements visualisation, fix a few frontend bugs
2021-05-31 Update front page
2021-05-31 Add model design files, restructure visualisation
2021-05-31 Sort sensor list
2021-06-03 Update deploy logic
2021-06-03 Add screenshots to documentation
2021-06-03 Deploying documentation to gh-pages from henriheimann/urban-climate-monitor@7456a6b8426c71a3b58804491ed9d038d47d9fbc
2021-06-03 Fix screen headings
2021-06-03 Deploying documentation to gh-pages from henriheimann/urban-climate-monitor@7868befe19bfac4bd314fb98a0088004f6171d69
2021-06-03 Fix image path
2021-06-03 Deploying documentation to gh-pages from henriheimann/urban-climate-monitor@804f458e242dfbaf0377b9751f4b70c74c42c6e7
2021-06-03 Update deployment for www. to non www redirect
2021-06-13 Update measurements scale, fix Safari shaders
2021-06-13 Update frontend pictures in documentation
2021-06-13 Deploying documentation to gh-pages from henriheimann/urban-climate-monitor@0466f9e7d74274f47b4f24bdced6cc8d7d495ccb
2021-06-13 Finish quick start section, add BOM
2021-06-13 Deploying documentation to gh-pages from henriheimann/urban-climate-monitor@e15a88ffa411b8789d60ab973154dec0c8780951
2021-06-13 Add additional paragaphs to backend and frontend documentation
2021-06-13 Deploying documentation to gh-pages from henriheimann/urban-climate-monitor@75386f96b1e6b389da57ce5a76b95eb7f7eace18
